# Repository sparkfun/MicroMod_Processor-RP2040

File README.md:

SparkFun MicroMod Processor RP2040
========================================

[*SparkFun MicroMod Processor RP2040 (DEV-17720)*](https://www.sparkfun.com/products/17720)

The SparkFun MicroMod Pi RP2040 Processor Board is a low-cost, high-performance board with flexible digital interfaces featuring the Raspberry Pi Foundation's RP2040 microcontroller. With the MicroMod M.2 connector, connecting your MicroMod Pi RP2040 Processor Board is a breeze. Simply match up the key on your processor's beveled edge connector to the key on the M.2 connector and secure it with a screw (included with all Carrier Boards).

Repository Contents
-------------------

* **/Documentation** - Data sheets, additional product information
* **/Hardware** - Eagle design files (.brd, .sch)

Documentation
--------------

* **[Hookup Guide](https://learn.sparkfun.com/tutorials/1495)** - Basic hookup guide for the MicroMod Processor RP2040
* **[SparkFun Graphical Datasheets](https://github.com/sparkfun/Graphical_Datasheets)** - Graphical datasheets for various SparkFun products.

Product Versions
----------------

* [DEV-17720](https://www.sparkfun.com/products/17720) -  initial release

License Information
-------------------

This product is _**open source**_! 

Please review the LICENSE.md file for license information. 

If you have any questions or concerns on licensing, please contact technical support on our [SparkFun forums](https://forum.sparkfun.com/viewforum.php?f=152).

Distributed as-is; no warranty is given.

- Your friends at SparkFun.

_<COLLABORATION CREDIT>_

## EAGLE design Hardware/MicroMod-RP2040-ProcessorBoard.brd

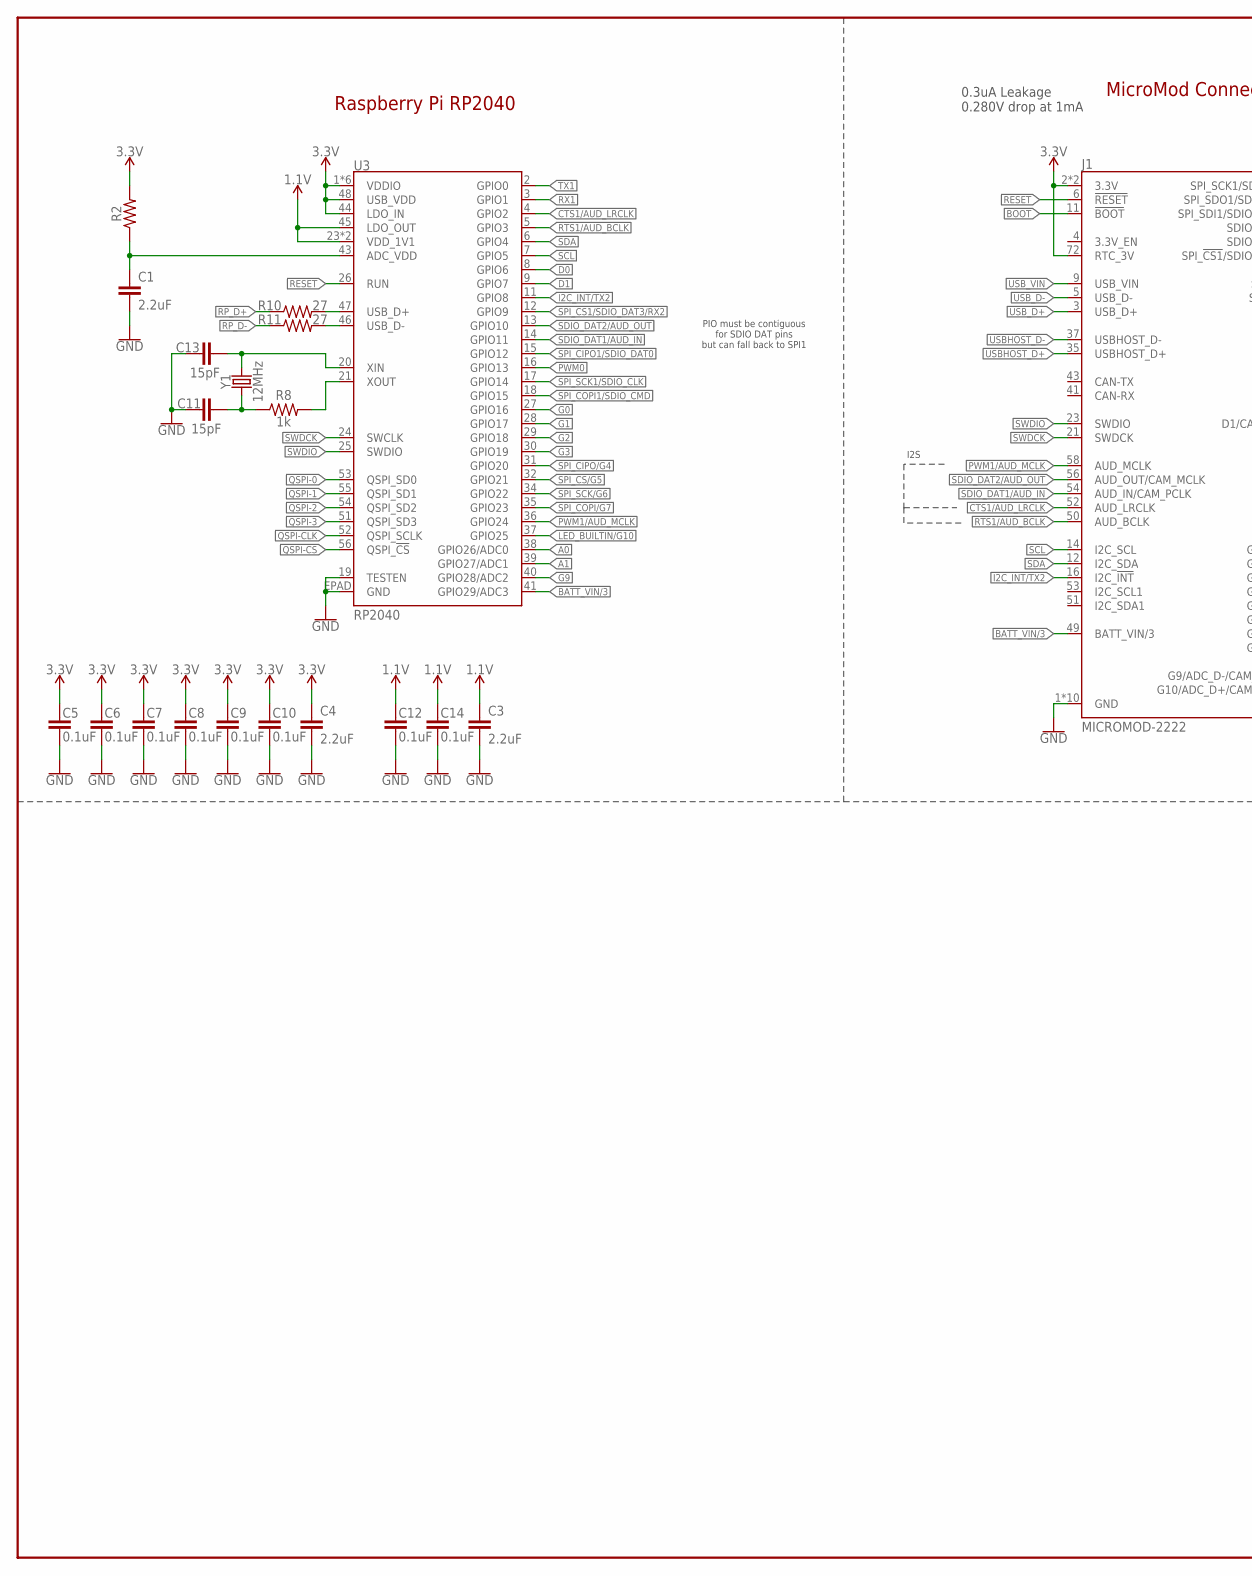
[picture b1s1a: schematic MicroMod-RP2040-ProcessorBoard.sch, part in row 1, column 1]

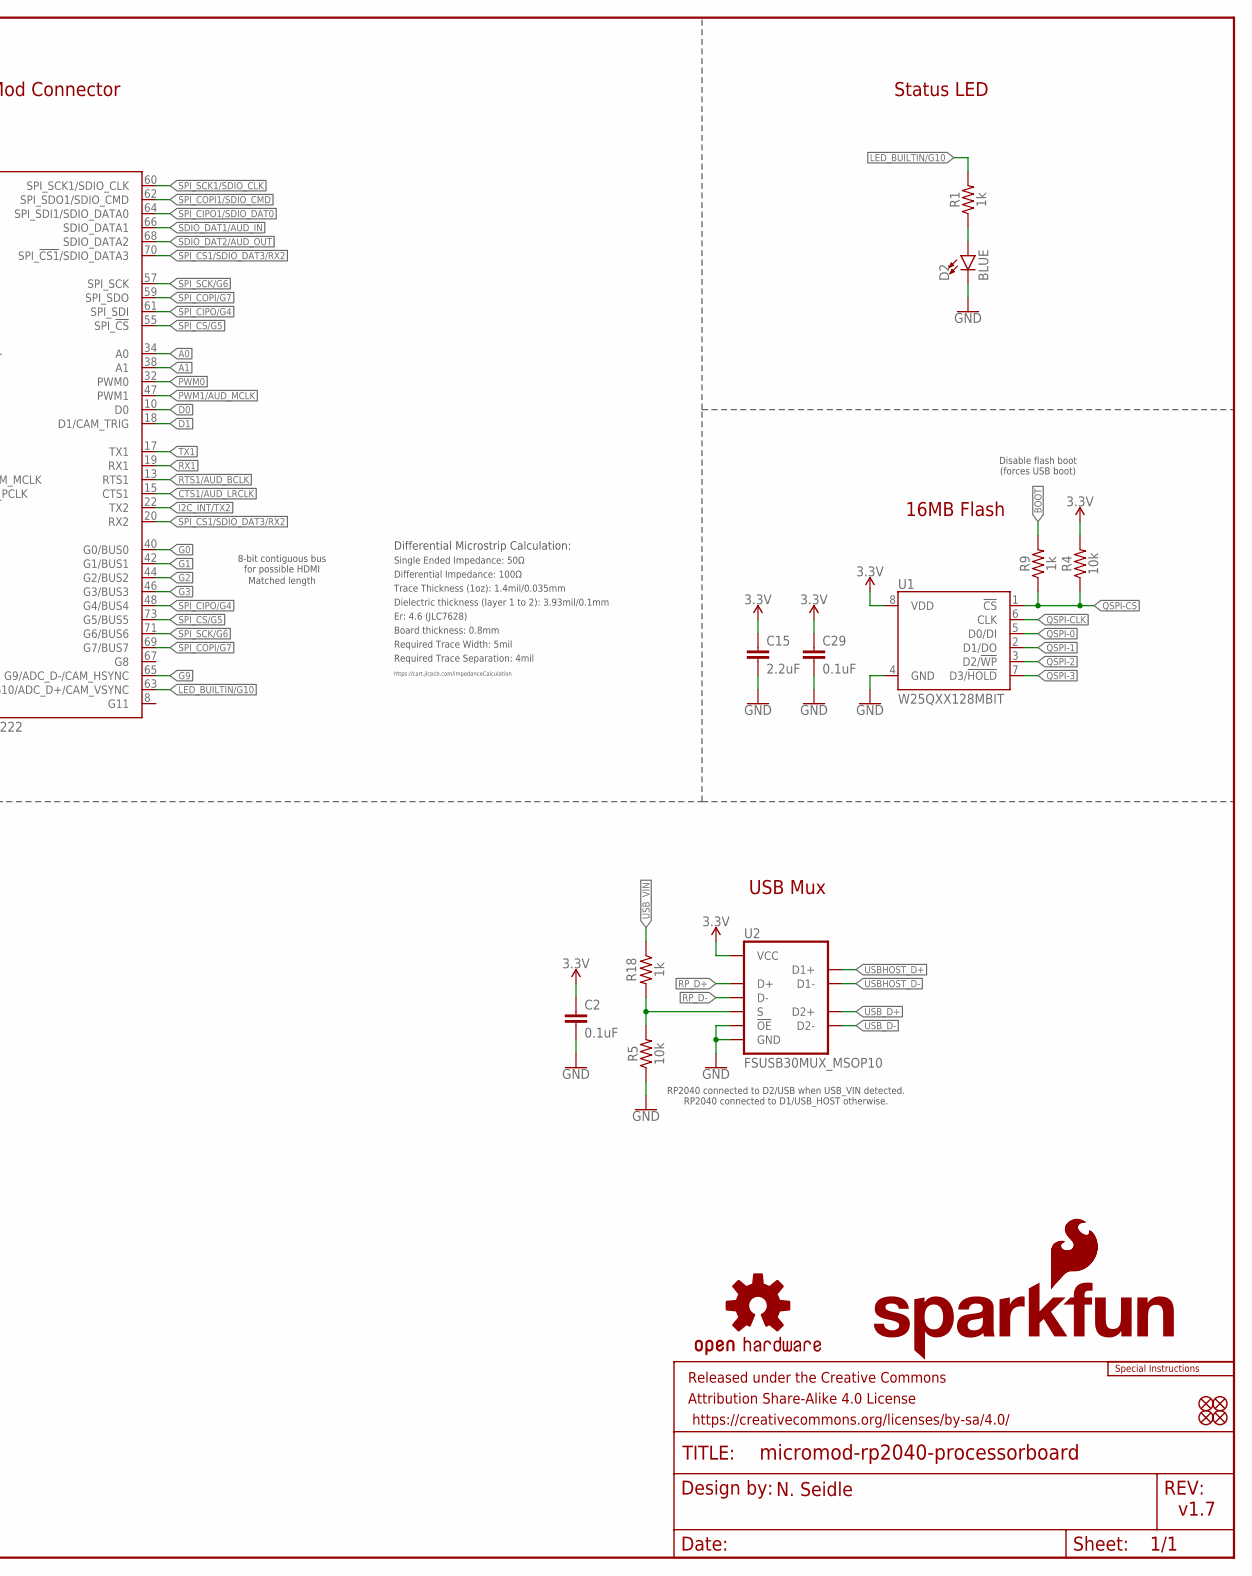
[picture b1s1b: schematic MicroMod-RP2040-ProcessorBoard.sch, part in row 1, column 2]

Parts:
C1, C3, C4, C15: 2.2uF; 0402-TIGHT
C2, C5, C6, C7, C8, C9, C10, C12, C14, C29: 0.1uF; 0402-TIGHT
C11, C13: 15pF; 0402-TIGHT
D2: BLUE; LED-0603
FD1, FD2, FD3, FD4: FIDUCIALUFIDUCIAL; FIDUCIAL-MICRO
FRAME1: FRAME-LEDGER; CREATIVE_COMMONS
J1: MICROMOD-2222; M.2-CARD-E-22
LOGO1: SFE_LOGO_NAME_FLAME.1_INCH; SFE_LOGO_NAME_FLAME_.1
LOGO2: SFE_LOGO_FLAME.1_INCH; SFE_LOGO_FLAME_.1
LOGO3: OSHW-LOGOMINI; OSHW-LOGO-MINI
LOGO4: SPECIAL_INSTRUCTIONS-ORDERING; ORDERING_INSTRUCTIONS
R1, R8, R9, R18: 1k; 0402-TIGHT
R2: 200OHM-0402T-1/16W-1%; 0402-TIGHT
R4, R5: 10k; 0402-TIGHT
R10, R11: 27; 0402-TIGHT
U1: W25QXX128MBIT; WSON-8-6X5-SKINNY_CENTERPAD
U2: FSUSB30MUX_MSOP10; MSOP10
U3: RP2040; QFN-56
Y1: 12MHz; CRYSTAL-SMD-2X2.5MM

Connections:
1.1V: C3.1, C12.1, C14.1, U3.23 (VDD_1V1), U3.45 (LDO_OUT), U3.50 (VDD_1V1)
3.3V: C2.1, C4.1, C5.1, C6.1, C7.1, C8.1, C9.1, C10.1, C15.1, C29.1, J1.2 (3.3V), J1.72 (RTC_3V), J1.74 (3.3V), R2.2, R4.2, U1.8 (VDD), U2.10 (VCC), U3.1 (VDDIO), U3.10 (VDDIO), U3.22 (VDDIO), U3.33 (VDDIO), U3.42 (VDDIO), U3.44 (LDO_IN), U3.48 (USB_VDD), U3.49 (VDDIO)
!RESET!: J1.6 (!RESET!), U3.26 (RUN)
A0: J1.34 (A0), U3.38 (GPIO26/ADC0)
A1: J1.38 (A1), U3.39 (GPIO27/ADC1)
ADC_VDD: C1.1, R2.1, U3.43 (ADC_VDD)
BATT_VIN/3: J1.49 (BATT_VIN/3), U3.41 (GPIO29/ADC3)
BOOT: J1.11 (!BOOT!), R9.2
CTS1/AUD_LRCLK: J1.15 (CTS1), J1.52 (AUD_LRCLK), U3.4 (GPIO2)
D0: J1.10 (D0), U3.8 (GPIO6)
D1: J1.18 (D1/CAM_TRIG), U3.9 (GPIO7)
G0: J1.40 (G0/BUS0), U3.27 (GPIO16)
G1: J1.42 (G1/BUS1), U3.28 (GPIO17)
G2: J1.44 (G2/BUS2), U3.29 (GPIO18)
G3: J1.46 (G3/BUS3), U3.30 (GPIO19)
G9: J1.65 (G9/ADC_D-/CAM_HSYNC), U3.40 (GPIO28/ADC2)
GND: C1.2, C2.2, C3.2, C4.2, C5.2, C6.2, C7.2, C8.2, C9.2, C10.2, C11.1, C12.2, C13.1, C14.2, C15.2, C29.2, D2.C, J1.1 (GND), J1.7 (GND), J1.33 (GND), J1.36 (GND), J1.39 (GND), J1.45 (GND), J1.75 (GND), J1.GND1 (GND), J1.GND2 (GND), J1.GND3 (GND), R5.1, U1.4 (GND), U2.5 (GND), U2.9 (!OE!), U3.19 (TESTEN), U3.EPAD (GND)
I2C_!INT!/TX2: J1.16 (I2C_!INT!), J1.22 (TX2), U3.11 (GPIO8)
LED_BUILTIN/G10: J1.63 (G10/ADC_D+/CAM_VSYNC), R1.2, U3.37 (GPIO25)
unnamed: D2.A, R1.1
unnamed: R8.2, U3.21 (XOUT)
unnamed: C13.2, U3.20 (XIN), Y1.P3 (2)
unnamed: C11.2, R8.1, Y1.P1 (1)
PWM0: J1.32 (PWM0), U3.16 (GPIO13)
PWM1/AUD_MCLK: J1.47 (PWM1), J1.58 (AUD_MCLK), U3.36 (GPIO24)
QSPI-0: U1.5 (D0/DI), U3.53 (QSPI_SD0)
QSPI-1: U1.2 (D1/DO), U3.55 (QSPI_SD1)
QSPI-2: U1.3 (D2/!WP!), U3.54 (QSPI_SD2)
QSPI-3: U1.7 (D3/!HOLD!), U3.51 (QSPI_SD3)
QSPI-CLK: U1.6 (CLK), U3.52 (QSPI_SCLK)
QSPI-CS: R4.1, R9.1, U1.1 (!CS!), U3.56 (QSPI_!CS!)
RP_D1+: R10.2, U3.47 (USB_D+)
RP_D1-: R11.2, U3.46 (USB_D-)
RP_D+: R10.1, U2.4 (D+)
RP_D-: R11.1, U2.6 (D-)
RTS1/AUD_BCLK: J1.13 (RTS1), J1.50 (AUD_BCLK), U3.5 (GPIO3)
RX1: J1.19 (RX1), U3.3 (GPIO1)
SCL: J1.14 (I2C_SCL), U3.7 (GPIO5)
SDA: J1.12 (I2C_SDA), U3.6 (GPIO4)
SDIO_DAT1/AUD_IN: J1.54 (AUD_IN/CAM_PCLK), J1.66 (SDIO_DATA1), U3.14 (GPIO11)
SDIO_DAT2/AUD_OUT: J1.56 (AUD_OUT/CAM_MCLK), J1.68 (SDIO_DATA2), U3.13 (GPIO10)
SPI_!CS1!/SDIO_DAT3/RX2: J1.20 (RX2), J1.70 (SPI_!CS1!/SDIO_DATA3), U3.12 (GPIO9)
SPI_!CS!/G5: J1.55 (SPI_!CS!), J1.73 (G5/BUS5), U3.32 (GPIO21)
SPI_CIPO1/SDIO_DAT0: J1.64 (SPI_SDI1/SDIO_DATA0), U3.15 (GPIO12)
SPI_CIPO/G4: J1.48 (G4/BUS4), J1.61 (SPI_SDI), U3.31 (GPIO20)
SPI_COPI1/SDIO_CMD: J1.62 (SPI_SDO1/SDIO_CMD), U3.18 (GPIO15)
SPI_COPI/G7: J1.59 (SPI_SDO), J1.69 (G7/BUS7), U3.35 (GPIO23)
SPI_SCK1/SDIO_CLK: J1.60 (SPI_SCK1/SDIO_CLK), U3.17 (GPIO14)
SPI_SCK/G6: J1.57 (SPI_SCK), J1.71 (G6/BUS6), U3.34 (GPIO22)
SWDCK: J1.21 (SWDCK), U3.24 (SWCLK)
SWDIO: J1.23 (SWDIO), U3.25 (SWDIO)
TX1: J1.17 (TX1), U3.2 (GPIO0)
USBHOST_D+: J1.35 (USBHOST_D+), U2.2 (D1+)
USBHOST_D-: J1.37 (USBHOST_D-), U2.8 (D1-)
USB_D+: J1.3 (USB_D+), U2.3 (D2+)
USB_D-: J1.5 (USB_D-), U2.7 (D2-)
USB_MUX_SIG: R5.2, R18.2, U2.1 (S)
USB_VIN: J1.9 (USB_VIN), R18.1

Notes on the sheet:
MicroMod Connector
v1.7
N. Seidle
Raspberry Pi RP2040
Status LED
16MB Flash
Disable flash boot (forces USB boot)
PIO must be contiguous for SDIO DAT pins but can fall back to SPI1
8-bit contiguous bus for possible HDMI
0.3uA Leakage 0.280V drop at 1mA
I2S
USB Mux
RP2040 connected to D2/USB when USB_VIN detected. RP2040 connected to D1/USB_HOST otherwise.
Board thickness: 0.8mm
Er: 4.6 (JLC7628)
Trace Thickness (1oz): 1.4mil/0.035mm
Single Ended Impedance: 50Ω
Dielectric thickness (layer 1 to 2): 3.93mil/0.1mm
https://cart.jlcpcb.com/impedanceCalculation
Differential Microstrip Calculation:
Required Trace Separation: 4mil
Required Trace Width: 5mil
Differential Impedance: 100Ω
Matched length

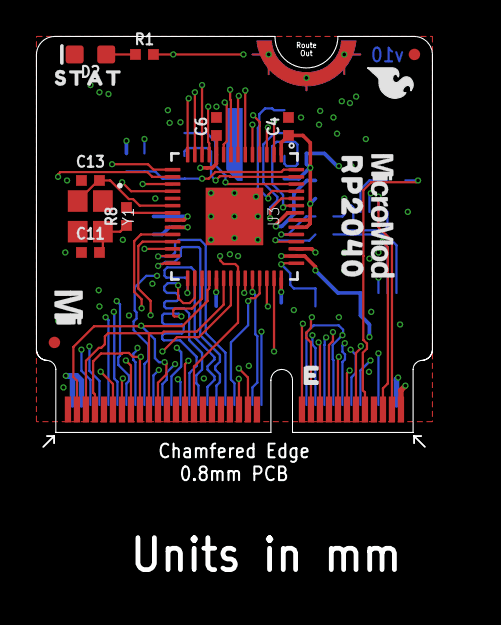
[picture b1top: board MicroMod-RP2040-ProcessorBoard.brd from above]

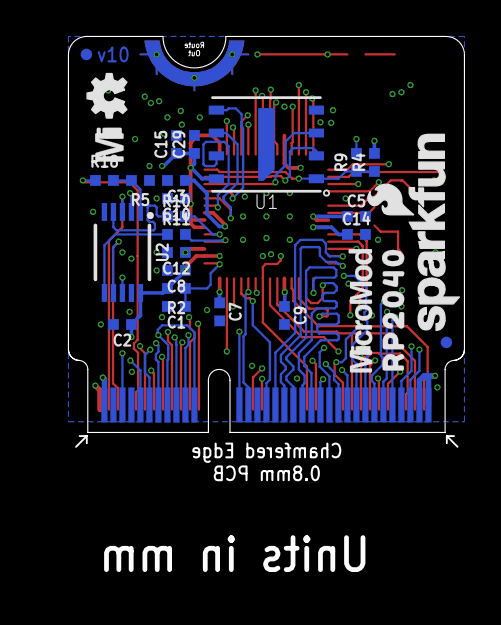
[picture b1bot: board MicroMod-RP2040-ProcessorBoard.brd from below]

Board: 4 copper layers, 22.0 x 22.8 mm, 47 parts (28 on the bottom side), 58 nets.

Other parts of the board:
U$1, U$7: MICROMOD_MI_LOGO_.35
U$3, U$12: MICROMOD_LOGO_.3
U$4, U$9: RP20400
U$11: STAT0

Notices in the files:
parts and their libraries:
SparkFun-Aesthetics: Licensing: Creative Commons ShareAlike 4.0 International - https://creativecommons.org/licenses/by-sa/4.0
SparkFun-Aesthetics: Released under the Creative Commons Attribution Share-Alike 4.0 License
SparkFun-Aesthetics: https://creativecommons.org/licenses/by-sa/4.0
